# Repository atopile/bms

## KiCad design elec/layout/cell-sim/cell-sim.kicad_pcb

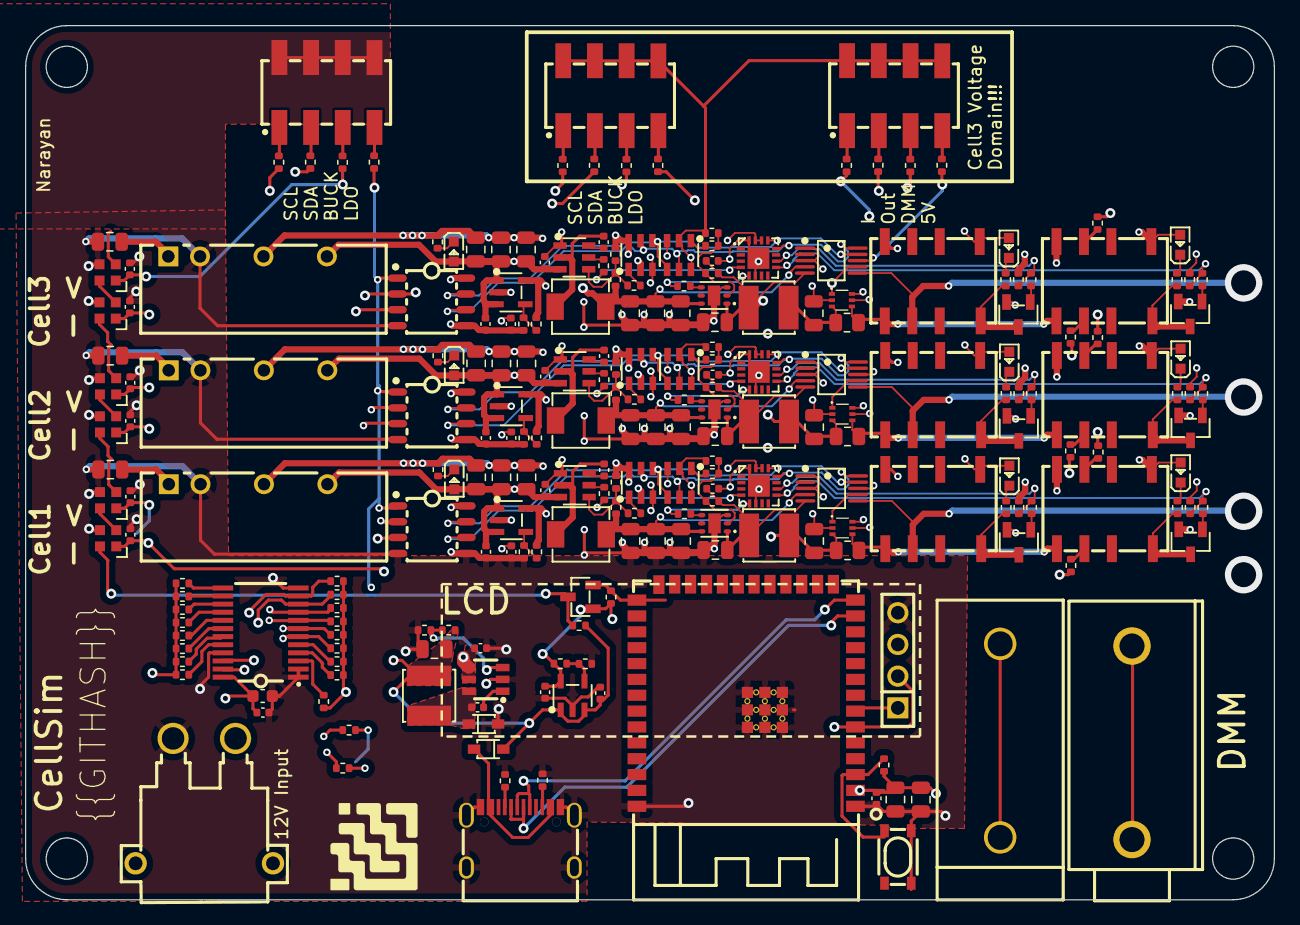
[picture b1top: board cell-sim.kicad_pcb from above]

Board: 4 copper layers, 100.0 x 70.0 mm, 238 parts (0 on the bottom side), 150 nets.

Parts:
C1, C4, C8, C15, C19, C23, C24, C31, C35, C39, C40, C47, C51, C55, C56: 16V 100nF X7R ±10% 0402 Multilayer Ceramic Capaci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; C0402
C2, C3, C7, C12, C13, C14, C16, C17, C18, C21, C22, C28, C29, C30, C32, C33, C34, C37, C38, C44, C45, C46, C48, C49, C50, C53, C54: 25V 10uF X5R ±10% 0805 Multilayer Ceramic Capacit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; C0805
C5: 16V 2.2uF X5R ±10% 0603 Multilayer Ceramic Capaci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; C0603
C6: 6.3V 10uF X5R ±20% 0402 Multilayer Ceramic Capaci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; C0402
C9, C10, C20, C25, C26, C36, C41, C42, C52, C57, C58: 25V 1uF X5R ±10% 0402 Multilayer Ceramic Capacito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; C0402
C11, C27, C43: 50V 2.2uF X5R ±10% 0805 Multilayer Ceramic Capaci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; C0805
DS1, DS2: SOD-323_L1.8-W1.3-LS2.5-RD
J1: CONN-TH_XT30PW-M
L1: IND-SMD_L4.0-W4.0
L2, L4, L6: IND-SMD_L4.4-W4.2
L3, L5, L7: 100uH; IND-SMD_L4.0-W4.0
LED1, LED2, LED3, LED4, LED5, LED6, LED7, LED8, LED9: LED0603-RD
Q1, Q2, Q3, Q4, Q5, Q6: SOT-23-3_L2.9-W1.3-P1.90-LS2.4-BR
R1, R4, R5, R6, R7, R8, R9, R10, R11, R12, R13, R14, R15, R16, R17, R18, R19, R20, R27, R28, R32, R33, R36, R37, R40, R43, R47, R48, R52, R53, R56, R57, R60, R63, R67, R68, R72, R73, R76, R77, R80, R83, R87, R88: 62.5mW Thick Film Resistors 50V ±100ppm/℃ ±1% 10k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; R0402
R2, R3: 62.5mW Thick Film Resistors 50V ±100ppm/℃ ±1% 4.7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; R0402
R21, R22: 62.5mW Thick Film Resistors 50V ±100ppm/℃ ±1% 2.2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; R0402
R23: 62.5mW Thick Film Resistors 50V ±1% ±200ppm/℃ 22.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; R0402
R24: 62.5mW Thick Film Resistors 50V ±1% ±100ppm/℃ 4.1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; R0402
R25: 62.5mW Thick Film Resistors 50V ±100ppm/℃ ±1% 17.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; R0402
R26: 62.5mW Thick Film Resistors 50V ±100ppm/℃ ±1% 10.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; R0402
R29, R39, R42, R49, R59, R62, R69, R79, R82: 62.5mW Thick Film Resistors 50V ±100ppm/℃ ±1% 21k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; R0402
R30, R50, R70: 62.5mW Thick Film Resistors 50V ±100ppm/℃ ±1% 24k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; R0402
R31, R51, R71: 62.5mW Thick Film Resistors 50V ±100ppm/℃ ±1% 37.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; R0402
R34, R54, R74: 62.5mW Thick Film Resistors 50V ±100ppm/℃ ±1% 43k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; R0402
R35, R55, R75: 62.5mW Thick Film Resistors 50V ±100ppm/℃ ±1% 59k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; R0402
R38, R58, R78: 125mW Thick Film Resistors ±600ppm/℃ ±1% 110mΩ 08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; R0805
R41, R44, R61, R64, R81, R84, R89, R90, R91, R92, R93, R94, R95, R96, R97, R98, R99, R100: 62.5mW Thick Film Resistors 50V ±100ppm/℃ ±1% 1kΩ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; R0402
R45, R65, R85: 62.5mW Thick Film Resistors 50V ±100ppm/℃ ±1% 11.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; R0402
R46, R66, R86: 62.5mW Thick Film Resistors 50V ±100ppm/℃ ±1% 6.2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; R0402
U1: WIRELM-SMD_ESP32-S3-WROOM-1
U2: KEY-SMD_4P-L4.2-W3.2-P2.20-LS4.6
U3: USB-C-SMD_KH-TYPE-C-16P
U4: AUDIO-TH_24.243.1
U5: CONN-TH_24.243.2
U6: HDR-TH_4P-P2.54-V-F
U7: TSSOP-24_L7.8-W4.4-P0.65-LS6.4-BL
U8: SOT-23-6_L2.9-W1.6-P0.95-LS2.8-BR
U9, U24, U38, U52: SOT-23-5_L3.0-W1.7-P0.95-LS2.8-BL
U10: SOT-23-3_L2.9-W1.3-P1.90-LS2.4-BR
U11, U25, U39: PWRM-TH_BXXXXS-2WR2
U12, U26, U40: MSOP-10_L3.0-W3.0-P0.50-LS5.0-BL
U13, U14, U15, U27, U28, U29, U41, U42, U43: SOT-23-6_L2.9-W1.6-P0.95-LS2.8-BL
U16, U30, U44: WSON-6_L2.0-W2.0-P0.65-TL-EP
U17, U31, U45: SOT-563_L1.6-W1.2-P0.50-LS1.6-TL
U18, U19, U32, U33, U46, U47: RELAY-SMD_HFD4-5-SR
U20, U34, U48: QFN-16_L3.0-W3.0-P0.50-BL-EP1.7
U21, U35, U49: SOIC-8_L4.9-W3.9-P1.27-LS6.0-TL
U22, U23, U36, U37, U50, U51: LED-SMD_4P-L2.0-W2.0-BR
U53, U54, U55: HDR-SMD_8P-P2.54-V-M-R2-C4-LS7.4

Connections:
buck.feedback_div-out: R23.2, R24.1, U8.3
buck.ic-sw: C8.2, DS1.1, L1.1, U8.6
cb: C8.1, U8.1
cc1: R2.1, U3.A5
cc2: R3.1, U3.B5
cell1-gnd: C22.1, C28.2, C29.2, C30.2, C31.2, C32.2, C33.2, C34.2, C36.2, C37.2, C38.2, C41.2, C42.2, L3.2, Q3.2, Q4.2, R38.1, R49.2, R52.2, R56.2, R61.2, R64.2, R66.2, U17.3, U25.4, U26.1, U26.3, U27.2, U28.1, U29.2, U29.6, U30.3, U30.7, U31.2, U31.5, U32.4, U33.4, U34.6, U34.16, U34.17, U35.5, U38.2
cell1-led_data: U22.2, U37.4
cell1-scl: U12.10, U13.5, U15.5, U20.12, U21.6
cell1-sda: U12.9, U13.4, U15.4, U20.13, U21.7
cell1-vcc: U12.6, U18.6
cell1-vcc-1: C12.1, C13.1, C14.1, C15.1, C25.1, LED1.2, LED2.2, LED3.2, U11.6, U13.6, U14.3, U18.1, U19.1, U24.1, U24.3
cell1-vcc-2: C26.1, R45.1, U12.8, U13.3, U15.3, U17.6, U20.14, U20.15, U21.8, U24.5
cell1.adc-ain3: U12.7, U17.1
cell1.adc-vcc: C16.1, C17.1, C18.1, L2.2, R31.1, U12.4, U16.6
cell1.adc-vcc-1: C20.1, C21.1, L3.1, R35.1, U12.5, U16.1
cell1.buck-enable: R33.1, U20.4
cell1.buck.ctrl_resistor-vfb: R30.2, R31.2, R32.1, U14.4
cell1.buck.dac-vout: R30.1, U13.1
cell1.buck.regulator-en: R33.2, U14.5
cell1.buck.regulator-sw: C19.2, L2.1, U14.2
cell1.buck.regulator-vbst: C19.1, U14.6
cell1.current_sense.sensor-vcc: R38.2, U17.4, U18.5, U19.5
cell1.dmm_relay-gnd: R48.1, U19.3
cell1.dmm_relay-input: R43.1, R44.1, U20.9
cell1.dmm_relay-vcc: R47.1, U19.6
cell1.dmm_relay.fet-gate: Q2.1, R43.2
cell1.dmm_relay.indicator_led.resistor-cathode: LED3.1, R42.1
cell1.dmm_relay.relay-gnd: Q2.3, R42.2, U19.8
cell1.internal_ldo.feedback_div-out: R45.2, R46.1, U24.4
cell1.isolated_converter.led.resistor-cathode: LED1.1, R29.1
cell1.ldo-enable: R37.1, U20.5
cell1.ldo.ctrl_resistor-fb: R34.2, R35.2, R36.1, U16.2
cell1.ldo.dac-vout: R34.1, U15.1
cell1.ldo.regulator-en: R37.2, U16.4
cell1.output_relay-input: R40.1, R41.1, U20.10
cell1.output_relay.fet-gate: Q1.1, R40.2
cell1.output_relay.indicator_led.resistor-cathode: LED2.1, R39.1
cell1.output_relay.relay-gnd: Q1.3, R39.2, U18.8
cell1.voltage_led.ic-vcc: U22.4, U23.2
cell2-gnd-1: C38.1, C44.2, C45.2, C46.2, C47.2, C48.2, C49.2, C50.2, C52.2, C53.2, C54.2, C57.2, C58.2, L5.2, Q5.2, Q6.2, R58.1, R69.2, R72.2, R76.2, R81.2, R84.2, R86.2, U31.3, U39.4, U40.1, U40.3, U41.2, U42.1, U43.2, U43.6, U44.3, U44.7, U45.2, U45.5, U46.4, U47.4, U48.6, U48.16, U48.17, U49.5, U52.2, U54.2, U54.4, U54.6, U54.8, U55.2, U55.4, U55.6, U55.8
cell2-led_data: U36.2, U51.4
cell2-scl: U26.10, U27.5, U29.5, U34.12, U35.6
cell2-sda: U26.9, U27.4, U29.4, U34.13, U35.7
cell2-vcc: U26.6, U32.6
cell2-vcc-1: C28.1, C29.1, C30.1, C31.1, C41.1, LED4.2, LED5.2, LED6.2, U25.6, U27.6, U28.3, U32.1, U33.1, U38.1, U38.3
cell2-vcc-2: C42.1, R65.1, U26.8, U27.3, U29.3, U31.6, U34.14, U34.15, U35.8, U38.5
cell2.adc-ain3: U26.7, U31.1
cell2.adc-vcc: C32.1, C33.1, C34.1, L4.2, R51.1, U26.4, U30.6
cell2.adc-vcc-1: C36.1, C37.1, L5.1, R55.1, U26.5, U30.1
cell2.buck-enable: R53.1, U34.4
cell2.buck.ctrl_resistor-vfb: R50.2, R51.2, R52.1, U28.4
cell2.buck.dac-vout: R50.1, U27.1
cell2.buck.regulator-en: R53.2, U28.5
cell2.buck.regulator-sw: C35.2, L4.1, U28.2
cell2.buck.regulator-vbst: C35.1, U28.6
cell2.current_sense.sensor-vcc: R58.2, U31.4, U32.5, U33.5
cell2.dmm_relay-gnd: R68.1, U33.3
cell2.dmm_relay-input: R63.1, R64.1, U34.9
cell2.dmm_relay-vcc: R67.1, U33.6
cell2.dmm_relay.fet-gate: Q4.1, R63.2
cell2.dmm_relay.indicator_led.resistor-cathode: LED6.1, R62.1
cell2.dmm_relay.relay-gnd: Q4.3, R62.2, U33.8
cell2.internal_ldo.feedback_div-out: R65.2, R66.1, U38.4
cell2.isolated_converter.led.resistor-cathode: LED4.1, R49.1
cell2.ldo-enable: R57.1, U34.5
cell2.ldo.ctrl_resistor-fb: R54.2, R55.2, R56.1, U30.2
cell2.ldo.dac-vout: R54.1, U29.1
cell2.ldo.regulator-en: R57.2, U30.4
cell2.output_relay-input: R60.1, R61.1, U34.10
cell2.output_relay.fet-gate: Q3.1, R60.2
cell2.output_relay.indicator_led.resistor-cathode: LED5.1, R59.1
cell2.output_relay.relay-gnd: Q3.3, R59.2, U32.8
cell2.voltage_led.ic-vcc: U36.4, U37.2
cell3-scl: R93.1, U40.10, U41.5, U43.5, U48.12, U49.6
cell3-sda: R94.1, U40.9, U41.4, U43.4, U48.13, U49.7
cell3-vcc: C54.1, L7.2, R78.1, U45.3
cell3-vcc-1: C44.1, C45.1, C46.1, C47.1, C57.1, LED7.2, LED8.2, LED9.2, U39.6, U41.6, U42.3, U46.1, U47.1, U52.1, U52.3
cell3-vcc-2: C58.1, R85.1, R100.1, U40.8, U41.3, U43.3, U45.6, U48.14, U48.15, U49.8, U52.5
cell3.adc-ain3: R97.1, U40.7, U45.1
cell3.adc-vcc: C48.1, C49.1, C50.1, L6.2, R71.1, R95.1, U40.4, U44.6
cell3.adc-vcc-1: C52.1, C53.1, L7.1, R75.1, R96.1, U40.5, U44.1
cell3.buck-enable: R73.1, U48.4
cell3.buck.ctrl_resistor-vfb: R70.2, R71.2, R72.1, U42.4
cell3.buck.dac-vout: R70.1, U41.1
cell3.buck.regulator-en: R73.2, U42.5
cell3.buck.regulator-sw: C51.2, L6.1, U42.2
cell3.buck.regulator-vbst: C51.1, U42.6
cell3.current_sense.sensor-vcc: R78.2, U45.4, U46.5, U47.5
cell3.dmm_relay-gnd: R88.1, U47.3
cell3.dmm_relay-input: R83.1, R84.1, R99.1, U48.9
cell3.dmm_relay-vcc: R87.1, U47.6
cell3.dmm_relay.fet-gate: Q6.1, R83.2
cell3.dmm_relay.indicator_led.resistor-cathode: LED9.1, R82.1
cell3.dmm_relay.relay-gnd: Q6.3, R82.2, U47.8
cell3.internal_ldo.feedback_div-out: R85.2, R86.1, U52.4
cell3.isolated_converter.led.resistor-cathode: LED7.1, R69.1
cell3.ldo-enable: R77.1, U48.5
cell3.ldo.ctrl_resistor-fb: R74.2, R75.2, R76.1, U44.2
cell3.ldo.dac-vout: R74.1, U43.1
cell3.ldo.regulator-en: R77.2, U44.4
cell3.output_relay-input: R80.1, R81.1, R98.1, U48.10
cell3.output_relay.fet-gate: Q5.1, R80.2
cell3.output_relay.indicator_led.resistor-cathode: LED8.1, R79.1
cell3.output_relay.relay-gnd: Q5.3, R79.2, U46.8
cell3.voltage_led.ic-vcc: U50.4, U51.2
cell3_debug_1.header-_1: R93.2, U54.1
cell3_debug_1.header-_3: R94.2, U54.3
cell3_debug_1.header-_5: R95.2, U54.5
cell3_debug_1.header-_7: R96.2, U54.7
cell3_debug_2.header-_1: R97.2, U55.1
cell3_debug_2.header-_3: R98.2, U55.3
cell3_debug_2.header-_5: R99.2, U55.5
cell3_debug_2.header-_7: R100.2, U55.7
dm: U1.13, U3.A7, U3.B7
dp: U1.14, U3.A6, U3.B6
gnd: C1.2, C2.2, C3.2, C4.2, C5.2, C6.2, C7.2, C9.2, C10.2, C11.2, C12.2, C13.2, C14.2, C15.2, C16.2, C17.2, C18.2, C20.2, C21.2, C22.2, C23.2, C24.2, C25.2, C26.2, C27.2, C39.2, C40.2, C43.2, C55.2, C56.2, DS1.2, J1.1, Q1.2, Q2.2, R2.2, R3.2, R24.2, R26.2, R29.2, R32.2, R36.2, R41.2, R44.2, R46.2, U1.1, U1.40, U1.41, U2.3, U2.4, U3.1, U3.2, U3.3, U3.4, U3.A1, U3.A12, U3.B1, U3.B12, U6.4, U7.1, U7.2, U7.12, U7.21, U8.2, U9.2, U11.2, U11.4, U12.1, U12.3, U13.2, U14.1, U15.2, U15.6, U16.3, U16.7, U17.2, U17.5, U18.4, U19.4, U20.6, U20.16, U20.17, U21.4, U21.5, U22.3, U23.3, U24.2, U25.2, U35.4, U36.3, U37.3, U39.2, U49.4, U50.3, U51.3, U53.2, U53.4, U53.6, U53.8
gnd-2: R48.2, R68.2, R88.2, U5.1, U5.2
hv_signal: R28.2, U10.3, U23.4
i2c_debug.header-_1: R89.2, U53.1
i2c_debug.header-_3: R90.2, U53.3
i2c_debug.header-_5: R91.2, U53.5
i2c_debug.header-_7: R92.2, U53.7
io0: R27.2, U1.27, U10.2
ldo3v3.feedback_div-out: R25.2, R26.1, U9.4
micro.ic-en: R1.2, U1.3, U2.1, U2.2
micro.ic-scl: R22.1, R89.1, U1.6, U6.2, U7.22
micro.ic-sda: R21.1, R90.1, U1.7, U6.1, U7.23
mux.ic-scl: R5.2, U7.5
mux.ic-scl-1: R7.2, U7.7, U21.3
mux.ic-scl-2: R9.2, U7.9, U35.3
mux.ic-scl-3: R11.2, U7.11, U49.3
mux.ic-scl-4: R13.2, U7.14
mux.ic-scl-5: R15.2, U7.16
mux.ic-scl-6: R17.2, U7.18
mux.ic-scl-7: R19.2, U7.20
mux.ic-sda: R6.2, U7.4
mux.ic-sda-1: R8.2, U7.6, U21.2
mux.ic-sda-2: R10.2, U7.8, U35.2
mux.ic-sda-3: R12.2, U7.10, U49.2
mux.ic-sda-4: R14.2, U7.13
mux.ic-sda-5: R16.2, U7.15
mux.ic-sda-6: R18.2, U7.17
mux.ic-sda-7: R20.2, U7.19
reset_: R4.1, U7.3
usbc-vcc: DS2.2, U3.A4, U3.A9, U3.B4, U3.B9
vcc: C6.1, C11.1, C27.1, C43.1, J1.2, U8.4, U8.5, U11.1, U25.1, U39.1
vcc-1: U40.6, U46.6
vcc-2: C7.1, C9.1, C23.1, C24.1, C39.1, C40.1, C55.1, C56.1, DS2.1, L1.2, R23.1, R28.1, R91.1, U9.1, U9.3, U22.1, U23.1, U36.1, U37.1, U50.1, U51.1
vcc-3: C1.1, C2.1, C3.1, C4.1, C5.1, C10.1, R1.1, R4.2, R5.1, R6.1, R7.1, R8.1, R9.1, R10.1, R11.1, R12.1, R13.1, R14.1, R15.1, R16.1, R17.1, R18.1, R19.1, R20.1, R21.2, R22.2, R25.1, R27.1, R92.1, U1.2, U6.3, U7.24, U9.5, U10.1, U21.1, U35.1, U49.1
vcc-4: R47.2, R67.2, R87.2, U4.1, U4.2

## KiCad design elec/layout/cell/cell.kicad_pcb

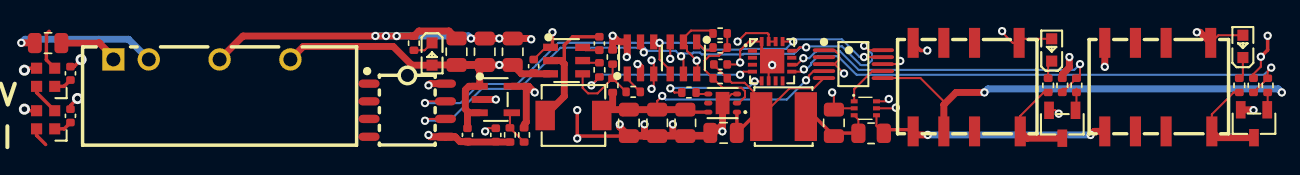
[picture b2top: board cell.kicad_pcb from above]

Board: 4 copper layers, 55 parts (0 on the bottom side), 36 nets.

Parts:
C1: 50V 2.2uF X5R ±10% 0805 Multilayer Ceramic Capaci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; C0805
C2, C3, C4, C6, C7, C8, C11, C12: 25V 10uF X5R ±10% 0805 Multilayer Ceramic Capacit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; C0805
C5, C9, C13, C14: 16V 100nF X7R ±10% 0402 Multilayer Ceramic Capaci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; C0402
C10, C15, C16: 25V 1uF X5R ±10% 0402 Multilayer Ceramic Capacito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; C0402
L1: IND-SMD_L4.4-W4.2
L2: 100uH; IND-SMD_L4.0-W4.0
LED1, LED2, LED3: LED0603-RD
Q1, Q2: SOT-23-3_L2.9-W1.3-P1.90-LS2.4-BR
R1, R11, R14: 62.5mW Thick Film Resistors 50V ±100ppm/℃ ±1% 21k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; R0402
R2: 62.5mW Thick Film Resistors 50V ±100ppm/℃ ±1% 24k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; R0402
R3: 62.5mW Thick Film Resistors 50V ±100ppm/℃ ±1% 37.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; R0402
R4, R5, R8, R9, R12, R15: 62.5mW Thick Film Resistors 50V ±100ppm/℃ ±1% 10k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; R0402
R6: 62.5mW Thick Film Resistors 50V ±100ppm/℃ ±1% 43k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; R0402
R7: 62.5mW Thick Film Resistors 50V ±100ppm/℃ ±1% 59k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; R0402
R10: 125mW Thick Film Resistors ±600ppm/℃ ±1% 110mΩ 08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; R0805
R13, R16: 62.5mW Thick Film Resistors 50V ±100ppm/℃ ±1% 1kΩ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; R0402
R17: 62.5mW Thick Film Resistors 50V ±100ppm/℃ ±1% 11.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; R0402
R18: 62.5mW Thick Film Resistors 50V ±100ppm/℃ ±1% 6.2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; R0402
U1: PWRM-TH_BXXXXS-2WR2
U2: MSOP-10_L3.0-W3.0-P0.50-LS5.0-BL
U3, U4, U5: SOT-23-6_L2.9-W1.6-P0.95-LS2.8-BL
U6: WSON-6_L2.0-W2.0-P0.65-TL-EP
U7: SOT-563_L1.6-W1.2-P0.50-LS1.6-TL
U8, U9: RELAY-SMD_HFD4-5-SR
U10: QFN-16_L3.0-W3.0-P0.50-BL-EP1.7
U11: SOIC-8_L4.9-W3.9-P1.27-LS6.0-TL
U12, U13: LED-SMD_4P-L2.0-W2.0-BR
U14: SOT-23-5_L3.0-W1.7-P0.95-LS2.8-BL

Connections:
adc-vcc: C6.1, C7.1, C8.1, L1.2, R3.1, U2.4, U6.6
adc-vcc-1: C10.1, C11.1, L2.1, R7.1, U2.5, U6.1
ain3: U2.7, U7.1
buck-enable: R5.1, U10.4
buck.dac-vout: R2.1, U3.1
buck.regulator-en: R5.2, U4.5
current_sense.sensor-vcc: R10.2, U7.4, U8.5, U9.5
dmm_relay-input: R15.1, R16.1, U10.9
dmm_relay.fet-gate: Q2.1, R15.2
dmm_relay.indicator_led.resistor-cathode: LED3.1, R14.1
dmm_relay.relay-gnd: Q2.3, R14.2, U9.8
fb: R6.2, R7.2, R8.1, U6.2
gnd: C1.2, U1.2
gnd-2: C13.2, C14.2, U12.3, U13.3
gnd-6: C2.2, C3.2, C4.2, C5.2, C6.2, C7.2, C8.2, C10.2, C11.2, C12.2, C15.2, C16.2, Q1.2, Q2.2, R1.2, R4.2, R8.2, R13.2, R16.2, R18.2, U1.4, U2.1, U2.3, U3.2, U3.6, U4.1, U5.2, U5.6, U6.3, U6.7, U7.2, U7.5, U8.4, U9.4, U10.6, U10.16, U10.17, U11.5, U14.2
isolated_converter.led.resistor-cathode: LED1.1, R1.1
ldo-enable: R9.1, U10.5
ldo.dac-vout: R6.1, U5.1
ldo.regulator-en: R9.2, U6.4
out: R17.2, R18.1, U14.4
output_relay-input: R12.1, R13.1, U10.10
output_relay.fet-gate: Q1.1, R12.2
output_relay.indicator_led.resistor-cathode: LED2.1, R11.1
output_relay.relay-gnd: Q1.3, R11.2, U8.8
scl-1: U2.10, U3.5, U5.5, U10.12, U11.6
sda-1: U2.9, U3.4, U5.4, U10.13, U11.7
sw: C9.2, L1.1, U4.2
vbst: C9.1, U4.6
vcc: C1.1, U1.1
vcc-1: U2.6, U8.6
vcc-2: C13.1, C14.1, U12.1, U13.1
vcc-5: C12.1, L2.2, R10.1, U7.3
vcc-6: C2.1, C3.1, C4.1, C5.1, C15.1, LED1.2, LED2.2, LED3.2, U1.6, U4.3, U8.1, U9.1, U14.1, U14.3
vcc-7: C16.1, R17.1, U2.8, U3.3, U5.3, U7.6, U10.14, U10.15, U11.8, U14.5
vfb: R2.2, R3.2, R4.1, U4.4
voltage_led.ic-vcc: U12.4, U13.2

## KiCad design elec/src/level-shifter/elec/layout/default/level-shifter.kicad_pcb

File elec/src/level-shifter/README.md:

# level-shifter

Wooohooo a new package!

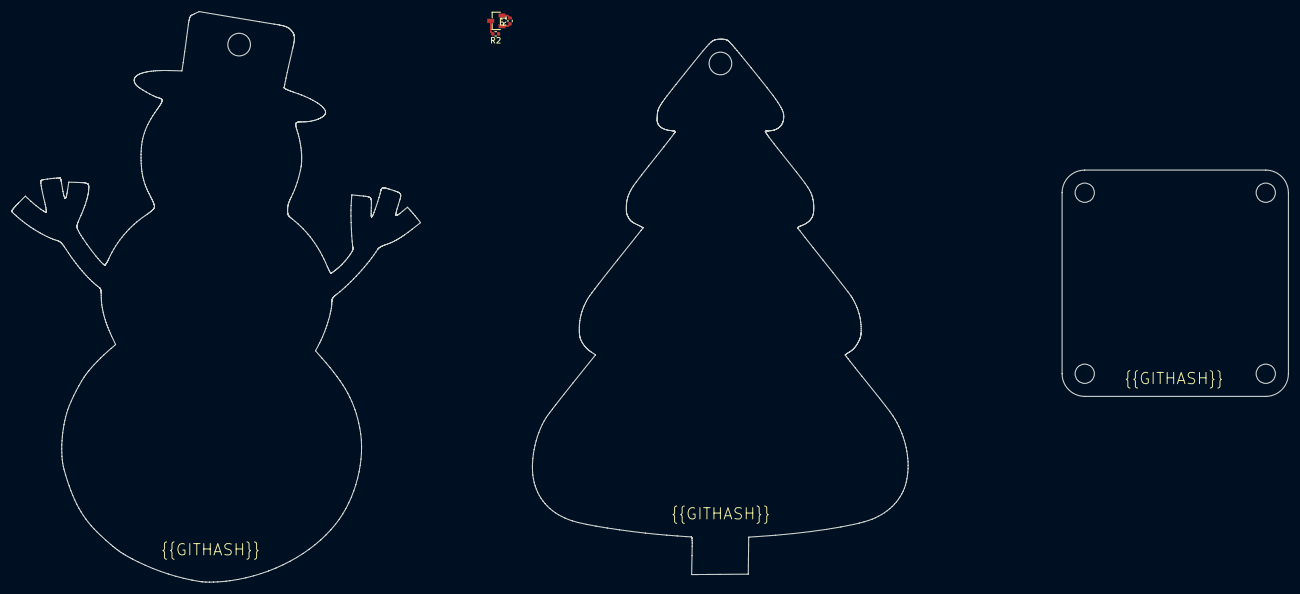
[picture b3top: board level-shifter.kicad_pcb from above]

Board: 2 copper layers, 3 parts (0 on the bottom side), 3 nets.

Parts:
R1, R2: Chip Resistor - Surface Mount 10KOhms ±5% 1/16W 0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; R0402
U1: SOT-23-3_L2.9-W1.3-P1.90-LS2.4-BR

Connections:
hv_signal: R2.2, U1.3
lv_signal: R1.2, U1.2
vcc: R1.1, U1.1

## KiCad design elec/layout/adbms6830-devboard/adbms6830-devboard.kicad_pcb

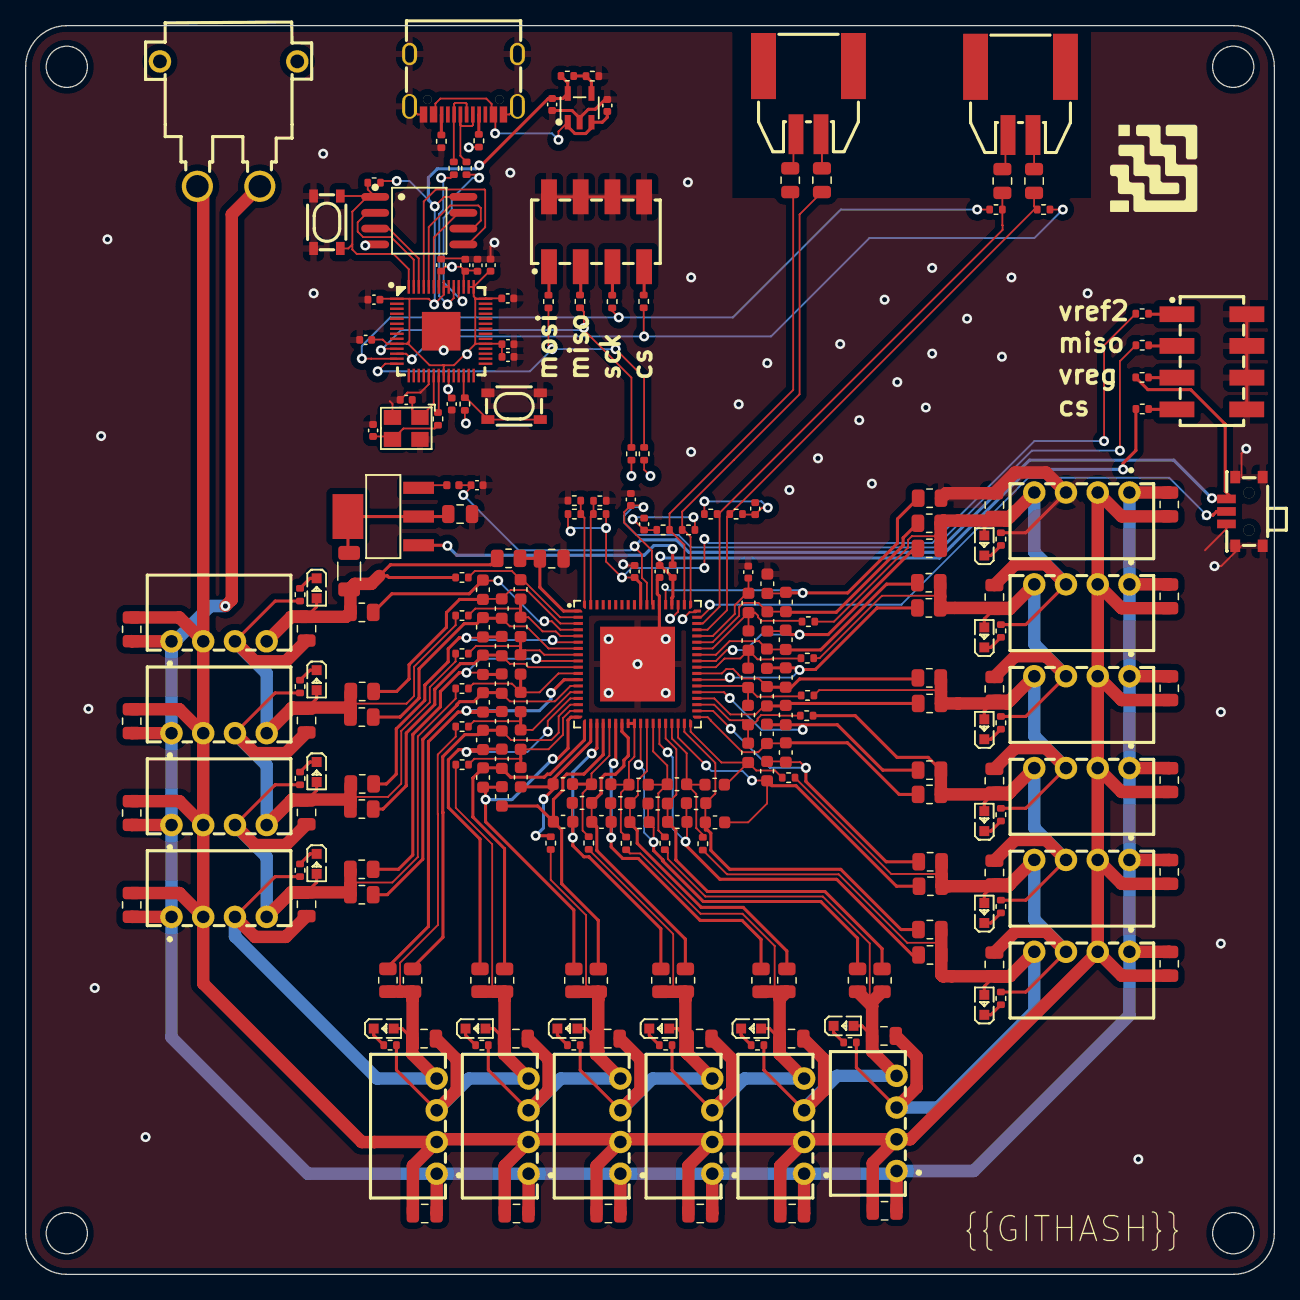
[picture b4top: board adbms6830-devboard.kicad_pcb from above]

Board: 4 copper layers, 100.0 x 100.0 mm, 251 parts (0 on the bottom side), 139 nets.

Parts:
C1, C2, C4, C5: 50V 47nF X7R ±10% 0805 Multilayer Ceramic Capacit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; C0805
C3, C6, C8: 50V 10nF X7R ±10% 0402 Multilayer Ceramic Capacit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; C0402
C7, C12: 50V 10nF X7R ±10% 0805 Multilayer Ceramic Capacit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; C0805
C9, C10, C11, C101, C105, C106, C107: 25V 1uF X5R ±10% 0402 Multilayer Ceramic Capacito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; C0402
C13, C17, C20, C23, C26, C29, C32, C35, C38, C41, C44, C47, C50, C53, C56, C59: 50V 10nF X7R ±10% 0603 Multilayer Ceramic Capacit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; C0603
C14, C15, C18, C19, C21, C22, C24, C25, C27, C28, C30, C31, C33, C34, C36, C37, C39, C40, C42, C43, C45, C46, C48, C49, C51, C52, C54, C55, C57, C58, C60, C61: 50V 100nF X7R ±10% 0603 Multilayer Ceramic Capaci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; C0603
C16, C96, C97, C98, C99, C100, C102, C103, C104: 16V 100nF X7R ±10% 0402 Multilayer Ceramic Capaci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; C0402
C62, C64, C66, C68, C70, C72, C74, C76, C78, C80, C82, C84, C86, C88, C90, C92: 50V 2.2uF X5R ±10% 0805 Multilayer Ceramic Capaci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; C0805
C63, C65, C67, C69, C71, C73, C75, C77, C79, C81, C83, C85, C87, C89, C91, C93: 25V 10uF X5R ±10% 0805 Multilayer Ceramic Capacit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; C0805
C94, C95: 50V 22pF C0G ±5% 0402 Multilayer Ceramic Capacito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; C0402
FB1: L0402
J1: CONN-TH_XT30PW-M
LED1, LED2, LED3, LED4, LED5, LED6, LED7, LED8, LED9, LED10, LED11, LED12, LED13, LED14, LED15, LED16: LED0603-RD
Q1: SOT-223-4_L6.5-W3.5-P2.30-LS7.0-BR
R1, R2, R3, R4: 62.5mW Thick Film Resistors 50V ±100ppm/℃ ±1% 49.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; R0402
R5: 250mW Thick Film Resistors 200V ±100ppm/℃ ±1% 300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; R1206
R6: 62.5mW Thick Film Resistors 50V ±1% ±200ppm/℃ 10Ω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; R0402
R7: 125mW Thick Film Resistors 150V ±100ppm/℃ ±1% 1kΩ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; R0805
R8, R11, R14, R17, R20, R23, R26, R29, R32, R35, R38, R41, R44, R47, R50, R53: 62.5mW Thick Film Resistors 50V ±100ppm/℃ ±1% 200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; R0402
R9, R10, R12, R13, R15, R16, R18, R19, R21, R22, R24, R25, R27, R28, R30, R31, R33, R34, R36, R37, R39, R40, R42, R43, R45, R46, R48, R49, R51, R52, R54, R55: 125mW Thick Film Resistors 150V ±1% ±200ppm/℃ 20Ω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; R0805
R56, R58: 100kohm +/- 1%; R0402
R57, R59: 62.5mW Thick Film Resistors 50V ±100ppm/℃ ±1% 100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; R0402
R60, R61, R62, R63, R64, R65, R66, R67, R68, R69, R70, R71, R72, R73, R74, R75: 62.5mW Thick Film Resistors 50V ±100ppm/℃ ±1% 3.4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; R0402
R76, R77: 62.5mW Thick Film Resistors 50V ±100ppm/℃ ±1% 10k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; R0402
R78, R89, R90, R91, R92, R93, R94, R95, R96: 62.5mW Thick Film Resistors 50V ±100ppm/℃ ±1% 1kΩ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; R0402
R79, R80: 62.5mW Thick Film Resistors 50V ±100ppm/℃ ±1% 27Ω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; R0402
R81, R82, R83, R84: 62.5mW Thick Film Resistors 50V ±1% ±200ppm/℃ 1Ω 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; R0402
R85, R86: 62.5mW Thick Film Resistors 50V ±100ppm/℃ ±1% 4.7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; R0402
R87: 62.5mW Thick Film Resistors 50V ±100ppm/℃ ±1% 17.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; R0402
R88: 62.5mW Thick Film Resistors 50V ±100ppm/℃ ±1% 10.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; R0402
U1: QFN-72_L10.0-W10.0-P0.50-BL-EP6.0_1
U2: SW-SMD_MSK12CO2
U3, U4, U5, U6, U7, U8, U9, U10, U11, U12, U13, U14, U15, U16, U17, U18: PWRM-TH_YLPTEC_BXXXXS-1WR3
U19: LQFN-56_L7.0-W7.0-P0.4-EP
U20, U21: KEY-SMD_4P-L4.2-W3.2-P2.20-LS4.6
U22: OSC-SMD_4P-L3.2-W2.5-BL
U23: SOIC-8_L5.3-W5.3-P1.27-LS8.0-BL
U24, U25: CONN-SMD_2P-P2.00_MOLEX_5023520201
U26: USB-C-SMD_KH-TYPE-C-16P
U27: SOT-23-5_L3.0-W1.7-P0.95-LS2.8-BL
U28, U29: HDR-SMD_8P-P2.54-V-M-R2-C4-LS7.4

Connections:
bms-n: C2.2, U24.2
bms-n-1: C5.2, U25.2
bms-p: C1.2, U24.1
bms-p-1: C4.2, U25.1
bms-vcc: C93.1, LED16.2, R5.1, R7.1, R53.1, R54.1, U18.4
bms.cell1-gnd: C63.1, C65.2, LED1.2, R8.1, R9.1, R13.1, R61.2, U3.4, U4.3
bms.cell2-gnd: C65.1, C67.2, LED2.2, R11.1, R12.1, R16.1, R62.2, U4.4, U5.3
bms.cell3-gnd: C67.1, C69.2, LED3.2, R14.1, R15.1, R19.1, R63.2, U5.4, U6.3
bms.cell4-gnd: C69.1, C71.2, LED4.2, R17.1, R18.1, R22.1, R64.2, U6.4, U7.3
bms.cell5-gnd: C71.1, C73.2, LED5.2, R20.1, R21.1, R25.1, R65.2, U7.4, U8.3
bms.cell6-gnd: C73.1, C75.2, LED6.2, R23.1, R24.1, R28.1, R66.2, U8.4, U9.3
bms.cell7-gnd: C75.1, C77.2, LED7.2, R26.1, R27.1, R31.1, R67.2, U9.4, U10.3
bms.cell8-gnd: C77.1, C79.2, LED8.2, R29.1, R30.1, R34.1, R68.2, U10.4, U11.3
bms.cell9-gnd: C79.1, C81.2, LED9.2, R32.1, R33.1, R37.1, R69.2, U11.4, U12.3
bms.cell10-gnd: C81.1, C83.2, LED10.2, R35.1, R36.1, R40.1, R70.2, U12.4, U13.3
bms.cell11-gnd: C83.1, C85.2, LED11.2, R38.1, R39.1, R43.1, R71.2, U13.4, U14.3
bms.cell12-gnd: C85.1, C87.2, LED12.2, R41.1, R42.1, R46.1, R72.2, U14.4, U15.3
bms.cell13-gnd: C87.1, C89.2, LED13.2, R44.1, R45.1, R49.1, R73.2, U15.4, U16.3
bms.cell14-gnd: C89.1, C91.2, LED14.2, R47.1, R48.1, R52.1, R74.2, U16.4, U17.3
bms.cell15-gnd: C91.1, C93.2, LED15.2, R50.1, R51.1, R55.1, R75.2, U17.4, U18.3
bms.ic-cs: C2.1, R2.2, R84.2, U1.51
bms.ic-gnd: C7.2, C8.2, C9.2, C10.2, C11.2, C12.2, C15.2, C16.2, C63.2, C94.2, C95.2, C96.2, C97.2, C98.2, C99.2, C100.2, C101.2, C102.2, C103.2, C104.2, C105.2, C106.2, C107.2, R10.1, R57.2, R59.2, R60.2, R85.2, R86.2, R88.2, U1.60, U1.73, U2.1, U2.4, U2.5, U3.3, U19.19, U19.57, U20.3, U20.4, U21.3, U21.4, U22.2, U22.4, U23.4, U26.1, U26.2, U26.3, U26.4, U26.A1, U26.A12, U26.B1, U26.B12, U27.2, U28.2, U28.4, U28.6, U28.8, U29.2, U29.4, U29.6, U29.8
bms.ic-gpio1: R56.2, R57.1, U1.72
bms.ic-gpio2: R58.2, R59.1, U1.71
bms.ic-miso: R82.2, U1.57
bms.ic-mosi: R81.2, U1.54
bms.ic-sck: C1.1, R1.1, R83.2, U1.52
bms.ic-vcc: C11.1, R90.1, U1.61
bms.ic-vcc-1: C9.1, FB1.2, R91.1, U1.62, U2.3
bms.ic-vcc-2: C10.1, R56.1, R58.1, R89.1, U1.63
bms.iso_a_isolation.r_top-vcc: C3.1, R1.2, R2.1
bms.iso_b_isolation.r_top-vcc: C6.1, R3.2, R4.1
bms.npn-vcc: Q1.1, R6.1
bms_ref_debug.header-_1: R89.2, U28.1
bms_ref_debug.header-_3: R90.2, U28.3
bms_ref_debug.header-_5: R91.2, U28.5
bms_ref_debug.header-_7: R92.2, U28.7
bms_spi_debug.header-_1: R93.2, U29.1
bms_spi_debug.header-_3: R94.2, U29.3
bms_spi_debug.header-_5: R95.2, U29.5
bms_spi_debug.header-_7: R96.2, U29.7
c0: C13.2, C16.1, U1.50
c1: C13.1, C17.2, R8.2, U1.48
c2: C17.1, C20.2, R11.2, U1.45
c3: C20.1, C23.2, R14.2, U1.42
c4: C23.1, C26.2, R17.2, U1.39
c5: C26.1, C29.2, R20.2, U1.36
c6: C29.1, C32.2, R23.2, U1.33
c7: C32.1, C35.2, R26.2, U1.30
c9: C38.1, C41.2, R32.2, U1.23
c9n: C35.1, C38.2, R29.2, U1.26, U1.27
c10: C41.1, C44.2, R35.2, U1.20
c11: C44.1, C47.2, R38.2, U1.17
c12: C47.1, C50.2, R41.2, U1.14
c13: C50.1, C53.2, R44.2, U1.11
c14: C53.1, C56.2, R47.2, U1.8
c15: C56.1, C59.2, R50.2, U1.5
c16: C59.1, R53.2, U1.2
cc1: R85.1, U26.A5
cc2: R86.1, U26.B5
cell_sim-gnd: C62.2, C64.2, C66.2, C68.2, C70.2, C72.2, C74.2, C76.2, C78.2, C80.2, C82.2, C84.2, C86.2, C88.2, C90.2, C92.2, J1.1, U3.1, U4.1, U5.1, U6.1, U7.1, U8.1, U9.1, U10.1, U11.1, U12.1, U13.1, U14.1, U15.1, U16.1, U17.1, U18.1
cell_sim-vcc: C62.1, C64.1, C66.1, C68.1, C70.1, C72.1, C74.1, C76.1, C78.1, C80.1, C82.1, C84.1, C86.1, C88.1, C90.1, C92.1, J1.2, U3.2, U4.2, U5.2, U6.2, U7.2, U8.2, U9.2, U10.2, U11.2, U12.2, U13.2, U14.2, U15.2, U16.2, U17.2, U18.2
cell_sim.cell1.led.resistor-cathode: LED1.1, R60.1
cell_sim.cell2.led.resistor-cathode: LED2.1, R61.1
cell_sim.cell3.led.resistor-cathode: LED3.1, R62.1
cell_sim.cell4.led.resistor-cathode: LED4.1, R63.1
cell_sim.cell5.led.resistor-cathode: LED5.1, R64.1
cell_sim.cell6.led.resistor-cathode: LED6.1, R65.1
cell_sim.cell7.led.resistor-cathode: LED7.1, R66.1
cell_sim.cell8.led.resistor-cathode: LED8.1, R67.1
cell_sim.cell9.led.resistor-cathode: LED9.1, R68.1
cell_sim.cell10.led.resistor-cathode: LED10.1, R69.1
cell_sim.cell11.led.resistor-cathode: LED11.1, R70.1
cell_sim.cell12.led.resistor-cathode: LED12.1, R71.1
cell_sim.cell13.led.resistor-cathode: LED13.1, R72.1
cell_sim.cell14.led.resistor-cathode: LED14.1, R73.1
cell_sim.cell15.led.resistor-cathode: LED15.1, R74.1
cell_sim.cell16.led.resistor-cathode: LED16.1, R75.1
collector: C7.1, Q1.2, Q1.4, R5.2
dm: R80.1, U26.A7, U26.B7
dp: R79.2, U26.A6, U26.B6
emitter: FB1.1, Q1.3
imb: C5.1, R4.2, U1.55
io: C8.1, R6.2, R92.1, U1.58
io0: U19.53, U23.5
io1: U19.55, U23.2
io2: U19.54, U23.3
io3: U19.51, U23.7
ipb: C4.1, R3.1, U1.56
isomd: U1.53, U2.2
ldo3v3.feedback_div-out: R87.2, R88.1, U27.4
micro-cs: R84.1, R96.1, U19.12
micro-cs-1: R77.2, U19.56, U21.1, U21.2, U23.1
micro-miso: R82.1, R94.1, U19.11
micro-mosi: R81.1, R93.1, U19.14
micro-sck: R83.1, R95.1, U19.13
micro-sck-1: U19.52, U23.6
micro-vcc: C96.1, C97.1, C98.1, C99.1, C100.1, C101.1, C107.1, R76.1, R77.1, R87.1, U19.1, U19.10, U19.22, U19.33, U19.42, U19.43, U19.44, U19.48, U19.49, U23.8, U27.5
micro.micro-vcc: C102.1, C103.1, C104.1, C105.1, U19.23, U19.45, U19.50
micro.osc.osc-out: C95.1, R78.2, U22.3
run: R76.2, U19.26, U20.1, U20.2
s1n: C14.2, C15.1, R10.2, U1.59
s1p: C14.1, C19.2, R9.2, U1.49
s2n: C18.2, C19.1, R13.2, U1.46
s2p: C18.1, C22.2, R12.2, U1.47
s3n: C21.2, C22.1, R16.2, U1.43
s3p: C21.1, C25.2, R15.2, U1.44
s4n: C24.2, C25.1, R19.2, U1.40
s4p: C24.1, C28.2, R18.2, U1.41
s5n: C27.2, C28.1, R22.2, U1.37
s5p: C27.1, C31.2, R21.2, U1.38
s6n: C30.2, C31.1, R25.2, U1.34
s6p: C30.1, C34.2, R24.2, U1.35
s7n: C33.2, C34.1, R28.2, U1.31
s7p: C33.1, C37.2, R27.2, U1.32
s8n: C36.2, C37.1, R31.2, U1.28
s8p: C36.1, C40.2, R30.2, U1.29
s9n: C39.2, C40.1, R34.2, U1.24
s9p: C39.1, C43.2, R33.2, U1.25
s10n: C42.2, C43.1, R37.2, U1.21
s10p: C42.1, C46.2, R36.2, U1.22
s11n: C45.2, C46.1, R40.2, U1.18
s11p: C45.1, C49.2, R39.2, U1.19
s12n: C48.2, C49.1, R43.2, U1.15
s12p: C48.1, C52.2, R42.2, U1.16
s13n: C51.2, C52.1, R46.2, U1.12
s13p: C51.1, C55.2, R45.2, U1.13
s14n: C54.2, C55.1, R49.2, U1.9
s14p: C54.1, C58.2, R48.2, U1.10
s15n: C57.2, C58.1, R52.2, U1.6
s15p: C57.1, C61.2, R51.2, U1.7
s16n: C60.2, C61.1, R55.2, U1.3
s16p: C60.1, R54.2, U1.4
usb_dm: R80.2, U19.46
usb_dp: R79.1, U19.47
usbc-vcc: C106.1, U26.A4, U26.A9, U26.B4, U26.B9, U27.1, U27.3
vp: C12.1, R7.2, U1.1
xin: C94.1, U19.20, U22.1
xout: R78.1, U19.21

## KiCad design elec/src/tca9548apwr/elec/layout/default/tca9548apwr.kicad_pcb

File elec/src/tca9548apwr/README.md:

# tca9548apwr

Wooohooo a new package!

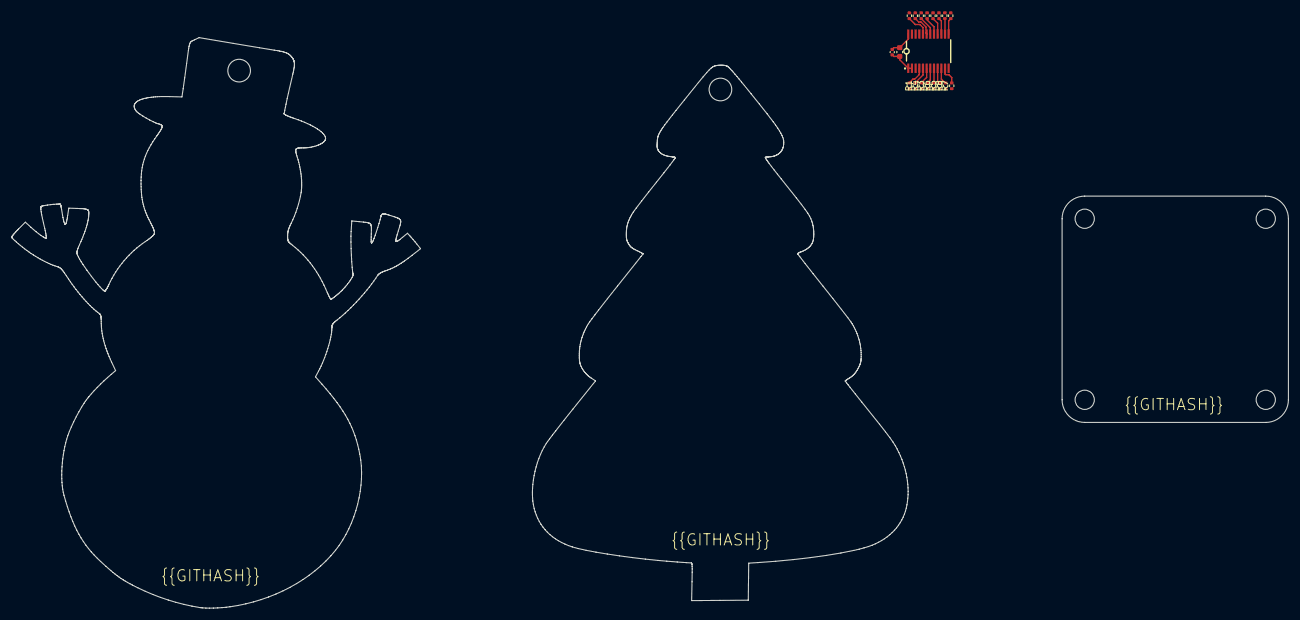
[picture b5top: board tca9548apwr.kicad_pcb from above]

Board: 2 copper layers, 19 parts (0 on the bottom side), 18 nets.

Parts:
C1: Multilayer Ceramic Capacitors MLCC - SMD/SMT 100n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; C0402
C2: Multilayer Ceramic Capacitors MLCC - SMD/SMT 2.2u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; C0603
R1, R2, R3, R4, R5, R6, R7, R8, R9, R10, R11, R12, R13, R14, R15, R16: Chip Resistor - Surface Mount 10KOhms ±5% 1/16W 0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; R0402
U1: TSSOP-24_L7.8-W4.4-P0.65-LS6.4-BL

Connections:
gnd: C1.2, C2.2, U1.1, U1.2, U1.12, U1.21
scl: R1.2, U1.5
scl-1: R3.2, U1.7
scl-2: R5.2, U1.9
scl-3: R7.2, U1.11
scl-4: R9.2, U1.14
scl-5: R11.2, U1.16
scl-6: R13.2, U1.18
scl-7: R15.2, U1.20
sda: R2.2, U1.4
sda-1: R4.2, U1.6
sda-2: R6.2, U1.8
sda-3: R8.2, U1.10
sda-4: R10.2, U1.13
sda-5: R12.2, U1.15
sda-6: R14.2, U1.17
sda-7: R16.2, U1.19
vcc: C1.1, C2.1, R1.1, R2.1, R3.1, R4.1, R5.1, R6.1, R7.1, R8.1, R9.1, R10.1, R11.1, R12.1, R13.1, R14.1, R15.1, R16.1, U1.24

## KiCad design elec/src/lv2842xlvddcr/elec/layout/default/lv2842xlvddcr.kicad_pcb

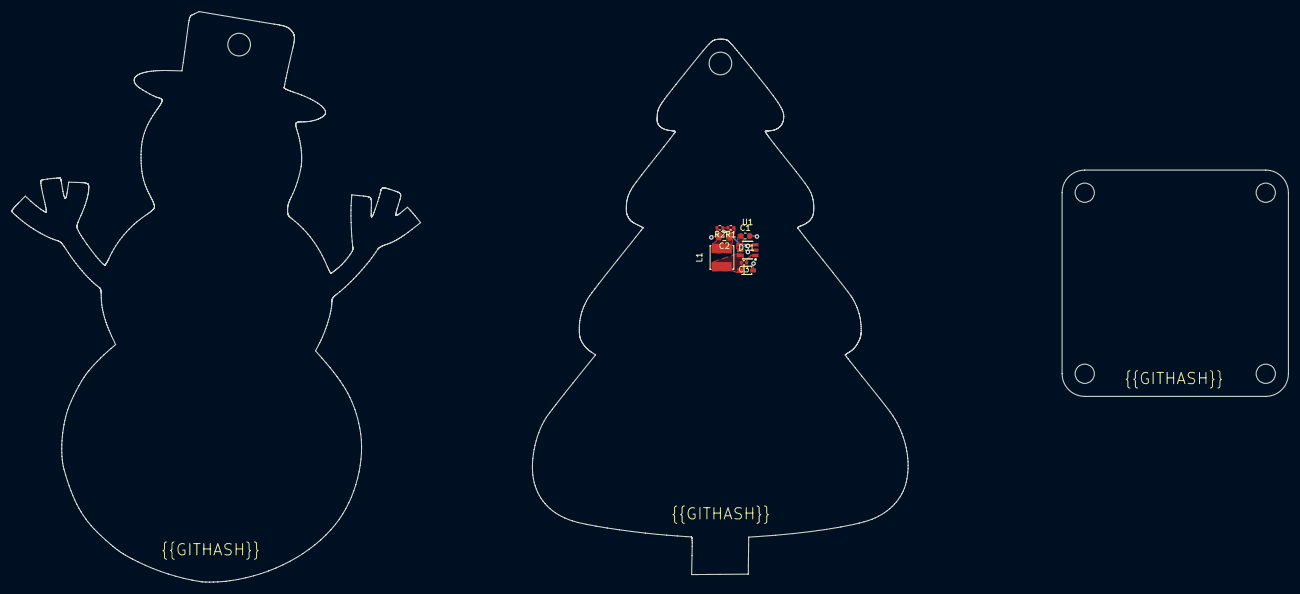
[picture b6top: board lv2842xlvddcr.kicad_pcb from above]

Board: 2 copper layers, 66.4 x 94.6 mm, 8 parts (0 on the bottom side), 6 nets.

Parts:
C1: 10V 10uF X5R ±10% 0603 Multilayer Ceramic Capacit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; C0603
C2: 25V 10uF X5R ±10% 0805 Multilayer Ceramic Capacit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; C0805
C3: 16V 100nF X7R ±10% 0402 Multilayer Ceramic Capaci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; C0402
DS1: SOD-323_L1.8-W1.3-LS2.5-RD
L1: IND-SMD_L4.0-W4.0
R1: 62.5mW Thick Film Resistors 50V ±100ppm/℃ ±1% 14.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; R0402
R2: 62.5mW Thick Film Resistors 50V ±100ppm/℃ ±1% 4.3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; R0402
U1: SOT-23-6_L2.9-W1.6-P0.95-LS2.8-BR

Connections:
cb: C3.1, U1.1
gnd: C1.2, C2.2, DS1.2, R2.2, U1.2
out: R1.2, R2.1, U1.3
sw: C3.2, DS1.1, L1.1, U1.6
vcc: C1.1, U1.4, U1.5
vcc-1: C2.1, L1.2, R1.1
